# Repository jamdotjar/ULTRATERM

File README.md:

# ULTRATERM

ULTRATERM is a miniature replica of an ULTRAKILL settings terminal ( like the one used in cybergrind ), that acts as a bluetooth audio player.

> ***NOTE**: This project is built, but there's still work to do. Check out the [journal](JOURNAL.md) for progress updates! Right now I'm:* `bashing together some code`

## Design

The terminal sits at around 125mm tall, with a 57x104mm footprint. It was designed to look cool, be fairly accurate, and act as a (mostly) stand alone device. It features a:
- 2.8" TFT display
- Touchscreen + 3 physical buttons
- A 2000mAh battery
- Bluetooth headphone support
- USB-C storage interface
- Removable SD card storage ( and a custom microSD card adapter )
The case is designed to be entirely 3D printable, and assembled without adhesive or fasteners.
While the terminal isn't a perfect replica, it's decently close. ( for example, there's none of the wires near the top, but there is a magnetic attachment point so I *can* add them )

This project was made as mostly a fun intro to custom hardware. I've made keyboards before, but design wise those are fairly simplec ( this isn't much more complicated ). I decided to model it after the ULTRAKILL Cybergrind terminal because that's the one that handles  cybergrind music ingame ( and because its form factor is also a *lot* more forgiving to fit everything into )

If you happen to try and make your own, I'd suggest either 3d-printing it in blue for minimum effort, or printing it in grey, painting it, then scuffing the paint to give it the worn look it has in-game. ( also check out the assembly section )

I'm still hacking away at getting everything working, but here's a video demo of my progress so far:

## Gallery

*more in [./gallery](gallery)*

## PCB

## Case

### Wiring

## BOM 
*prices in usd, see [bom.csv](/BOM.CSV) too*
|Item                                        |Quantity|Price|Supplier  |Notes                                                             |link                                                                                                      |
|--------------------------------------------|--------|-----|----------|------------------------------------------------------------------|----------------------------------------------------------------------------------------------------------|
|PCB                                         |5       |4.7  |JLCPCB    |                                                                  |https://jlcpcb.com/                                                                                       |
|TINYPICO v2                                 |1       |20 | Digikey   |(+20 dollar shipping, ik its really expensive, I csn cover a good bit of the cost )|https://www.mouser.com/ProductDetail/392-TP-01                      |
|TZT 240x320 2.8" SPI ST7789V LCD Touch Panel|1       |7.09 |Aliexpress|                                                                  |https://www.aliexpress.com/item/1005004557916570.html                                                     |
|3.7v 2000mah LiPo battery                   |1       |16.92|Amazon    |price comparable to ali                                           |https://www.amazon.ca/Rechargeable-Controller-CUH-ZCT1-Electronic-Bluetooth/dp/B0CG178SHB                 |
|Pin Headers                                 |20      |2.00 |Aliexpress|for stupid LCD mounting soln.                                     |https://www.aliexpress.com/item/4000873858801                                                             |
|22Awg wire                                  |5m      |2.4  |Aliexpress|front panel mount + battery backup soln                           |https://www.aliexpress.com/item/1005004712828392.html                                                     |
|32gb microSD card                           |2       |4.7  |LCSC      |second waives 3$ fee, saves 1 dollar on order total               |https://lcsc.com/product-detail/Storage-products_SDTRUVAL-SDSDQAD-016G-SDWCK_C42416577.html               |
|32gb SD card                                |1       |5.8  |LCSC      |                                                                  |https://lcsc.com/product-detail/Storage-products_MK-MKSD032G-CGT1A_C22374946.html                         |
|LM809                                       |1       |0.66 |LCSC      |                                                                  |https://lcsc.com/product-detail/Supervisor-and-Reset-ICs_Texas-Instruments-LM809M3X-4-38-NOPB_C544520.html|
|JST-PH-2                                    |10      |0.59 |LCSC      |                                                                  |https://lcsc.com/product-detail/Wire-To-Board-Connector_JST-B2B-PH-K-K-LF-SN_C265438.html                 |
|SPDT slide switch                           |20      |0.48 |LCSC      |                                                                  |https://lcsc.com/product-detail/Slide-Switches_SHOU-HAN-SK12D07VG4_C393937.html                           |
|6mm pushbutton                              |50      |0.84 |LCSC      |                                                                  |https://lcsc.com/product-detail/Tactile-Switches_SHOU-HAN-TS665CJ_C393938.html                            |
|Amphenol 10067847-001RLF                    |1       |1.31 |LCSC      |                                                                  |https://lcsc.com/product-detail/SD-Card-Memory-Card-Connector_Amphenol-ICC-10067847-001RLF_C569097.html   |
|Hirose C719027                              |1       |1.04 |LCSC      |                                                                  |https://lcsc.com/product-detail/SD-Card-Memory-Card-Connector_HRS-Hirose-DM3D-SF_C719027.html             |
|LCSC Shipping                               |        |12.88|LCSC      |                                                                  |                                                                                                          |
|Total                                       |1       |95.21|          |                                                                  |                                                                                                          |
## Assembly

Putting this together is relatively simple, the hardest part is connecting the screen and front panel before putting the two halves together. Assuming you aren't too rough, the mounting holes for the screen and button panels should be enough to hold them. A small dab of superglue can help make sure they don't come out with repeated use. I'd advise dupont cables or soemthing similar to connect the screen, as long as it has a lot of slack it should be fine ( the case has a lot of empty space to wind the cables into )

## LICENSE

This project uses the [CC-BY-SA-4.0](https://creativecommons.org/licenses/by-sa/4.0/) for all firmware, documentation, renders, and other writing. Hardware including all Case and PCB designs, is licensed under the [CERN-OHL-W v2](https://ohwr.org/cern_ohl_w_v2.txt)
> This project was heavily inspired by the game ULTRAKILL, created by Hakita (Arsi "Hakita" Patala). The ULTRATERM design, as well as some assets used in renders are derived from or inspired by ULTRAKILL.
All rights to ULTRAKILL belong to Hakita and New Blood Interactive. This project is not affiliated with or endorsed by Hakita or New Blood. 
( [ULTRAKILL is a banger game, you should totally get it, it's like 20 bucks ](http://devilmayquake.com))

This project was made for [*highway*](https://highway.hackclub.com)

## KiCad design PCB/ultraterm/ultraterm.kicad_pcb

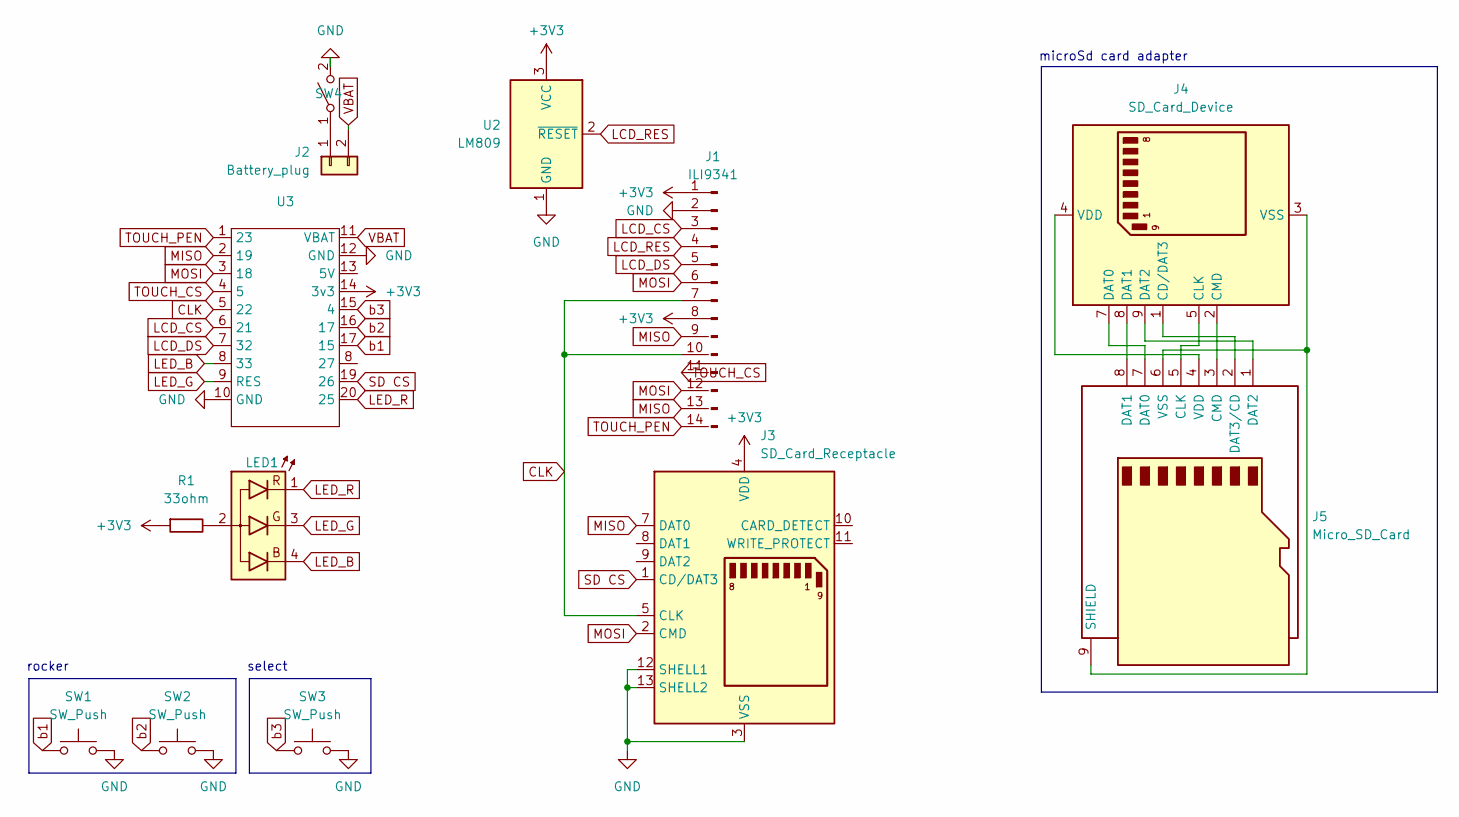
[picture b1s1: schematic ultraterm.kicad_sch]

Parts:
J1: ILI9341; PinHeader_1x11_P2.54mm_Vertical
J2: Battery_plug; JST_PH_B2B-PH-SM4-TB_1x02-1MP_P2.00mm_Vertical
J3: SD_Card_Receptacle; SD_Hirose_DM1AA_SF_PEJ82
J4: SD_Card_Device; SD_Card_Device_16mm_SlotDepth
J5: Micro_SD_Card; microSD_HC_Molex_104031-0811
LED1: LED_5mm_RGB_Kcom_RKGB; LED_D5.0mm-4_RGB_Wide_Pins
R1: 33ohm; R_Axial_DIN0207_L6.3mm_D2.5mm_P10.16mm_Horizontal
SW1, SW2, SW3: SW_Push; SW_PUSH_6mm
SW4: SW_SPST; SW_SPST_Omron_B3F-315x_Angled
U2: LM809; SOT-23
U3: TINYPICO

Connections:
+3V3: J1.1 (VCC), J1.8 (LED), J3.4 (VDD), R1.1, U2.3 (VCC), U3.14 (3v3)
CLK: J1.7 (SCK), J1.10 (CLK), J3.5 (CLK), U3.5 (22)
GND: J1.2 (GND), J3.3 (VSS), J3.6 (VSS), J3.12 (SHELL1), J3.13 (SHELL2), SW1.2, SW2.2, SW3.2, SW4.2 (B), U2.1 (GND), U3.10 (GND), U3.12 (GND)
LCD_CS: J1.3 (CS), U3.6 (21)
LCD_DS: J1.5 (DC/RS), U3.7 (32)
LCD_RES: J1.4 (RESET), U2.2 (~RESET)
LED_B: LED1.4 (B), U3.8 (33)
LED_G: LED1.3 (G), U3.9 (RES)
LED_R: LED1.1 (R), U3.20 (25)
MISO: J1.9 (MISO), J1.13 (T_DO), J3.7 (DAT0), U3.2 (19)
MOSI: J1.6 (MOSI), J1.12 (T_DIN), J3.2 (CMD), U3.3 (18)
unnamed: J2.1, SW4.1 (A)
unnamed: J4.1 (CD/DAT3), J5.2 (DAT3/CD)
unnamed: J4.5 (CLK), J5.5 (CLK)
unnamed: J4.2 (CMD), J5.3 (CMD)
unnamed: J4.7 (DAT0), J5.7 (DAT0)
unnamed: J4.8 (DAT1), J5.8 (DAT1)
unnamed: J4.9 (DAT2), J5.1 (DAT2)
unnamed: J4.4 (VDD), J5.4 (VDD)
unnamed: J4.3 (VSS), J4.6 (VSS), J5.6 (VSS), J5.9 (SHIELD)
unnamed: LED1.2 (A), R1.2
SD CS: J3.1 (CD/DAT3), U3.19 (26)
TOUCH_CS: J1.11 (T_CS), U3.4 (5)
TOUCH_PEN: J1.14 (T_IRQ), U3.1 (23)
VBAT: J2.2, U3.11 (VBAT)
b1: SW1.1, U3.17 (15)
b2: SW2.1, U3.16 (17)
b3: SW3.1, U3.15 (4)

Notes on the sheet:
microSd card adapter
rocker
select

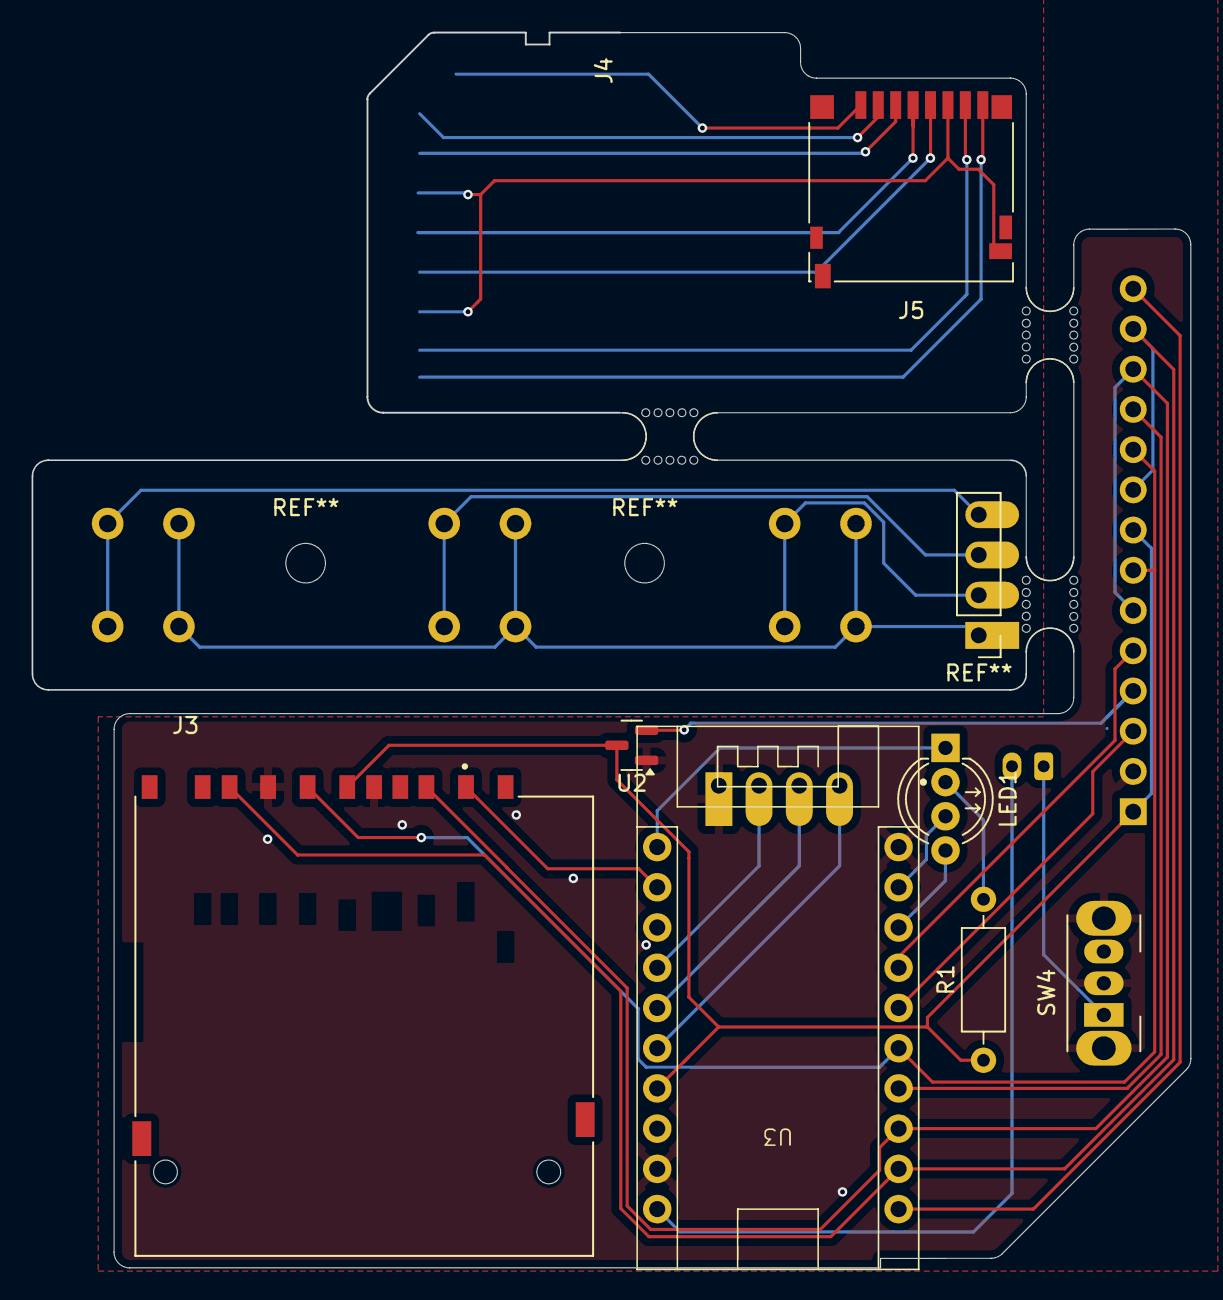
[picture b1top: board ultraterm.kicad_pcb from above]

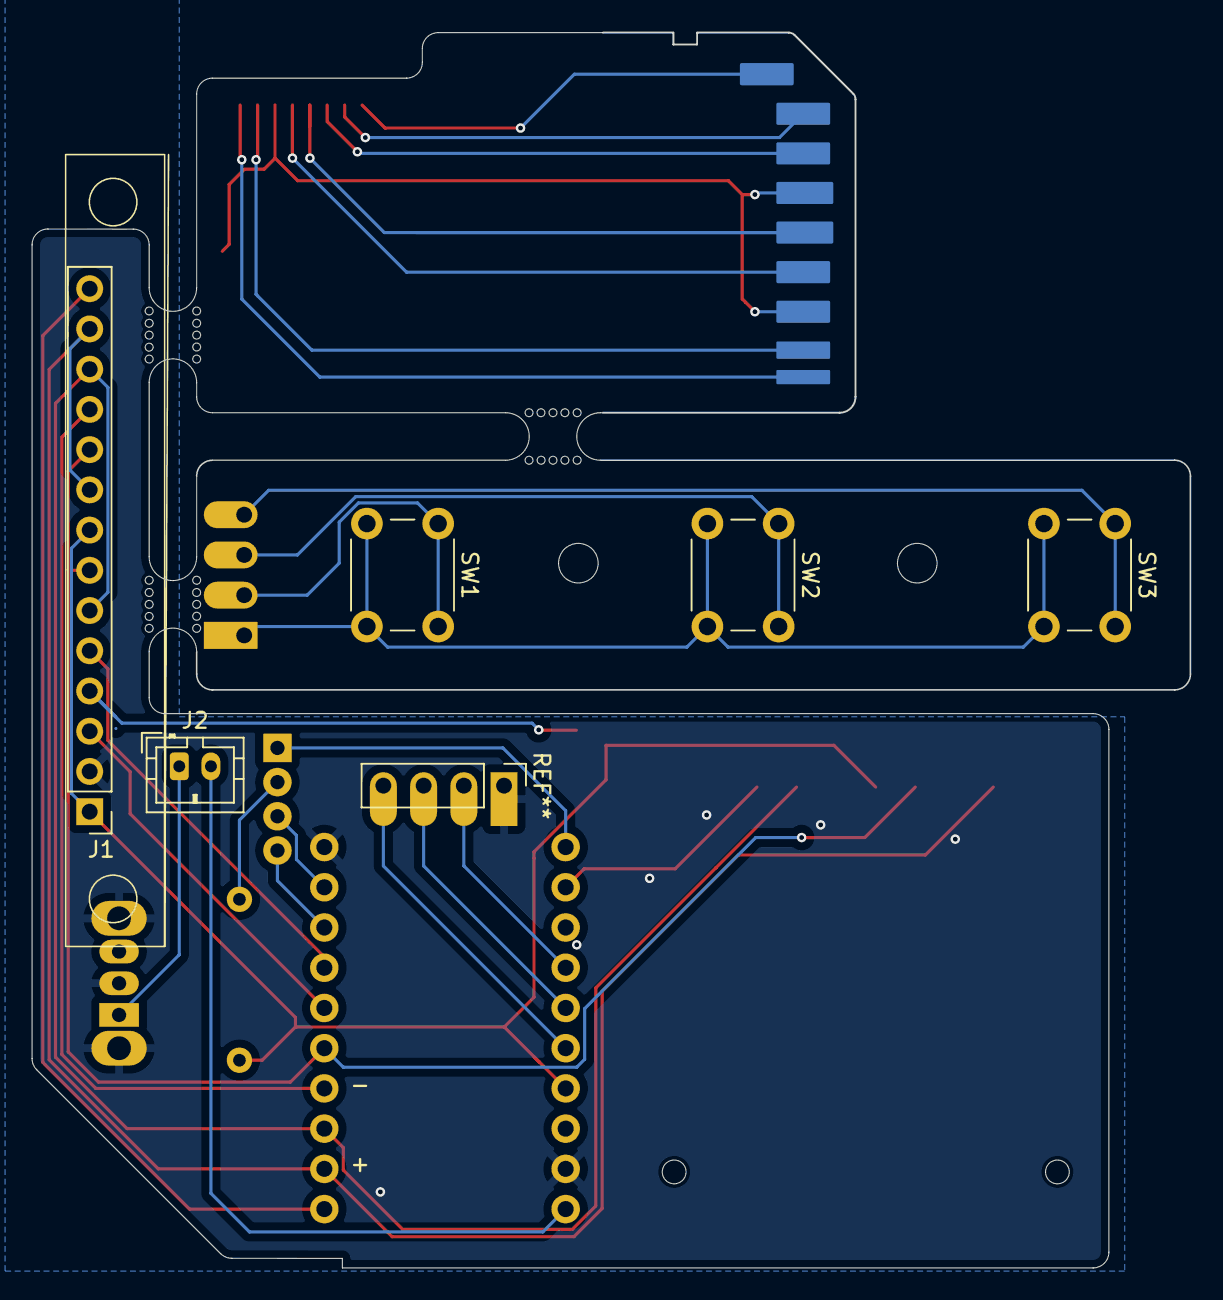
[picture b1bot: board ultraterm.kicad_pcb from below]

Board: 2 copper layers, 73.1 x 78.0 mm, 16 parts (5 on the bottom side), 28 nets.

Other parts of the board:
mouse-bite-3mm-slot, mouse-bite-3mm-slot#2, mouse-bite-3mm-slot#3: VAL**; mouse-bite-3mm-slot

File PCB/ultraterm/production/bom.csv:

Designator,Footprint,Quantity,Value,LCSC Part #
J1,PinHeader_1x14_P2.54mm_Vertical,1,ILI9341,
J2,JST_PH_B2B-PH-K_1x02_P2.00mm_Vertical,1,Battery_plug,
J3,AMPHENOL_10067847-001RLF,1,SD_Card_Receptacle,
J4,SD_Card_Device_16mm_SlotDepth,1,SD_Card_Device,
J5,microSD_HC_Hirose_DM3D-SF,1,Micro_SD_Card,
"MOUSE-BITE-3MM-SLOT_3, MOUSE-BITE-3MM-SLOT_2, MOUSE-BITE-3MM-SLOT",mouse-bite-3mm-slot,3,VAL**,
"SW1, SW2, SW3",SW_PUSH_6mm,3,SW_Push,
SW4,SW_Slide_SPDT_Angled_CK_OS102011MA1Q,1,SW_SPST,
U1,XIAO-ESP32S3-SMD,1,XIAO-ESP32-S3-SMD,
U2,SOT-23,1,LM809,

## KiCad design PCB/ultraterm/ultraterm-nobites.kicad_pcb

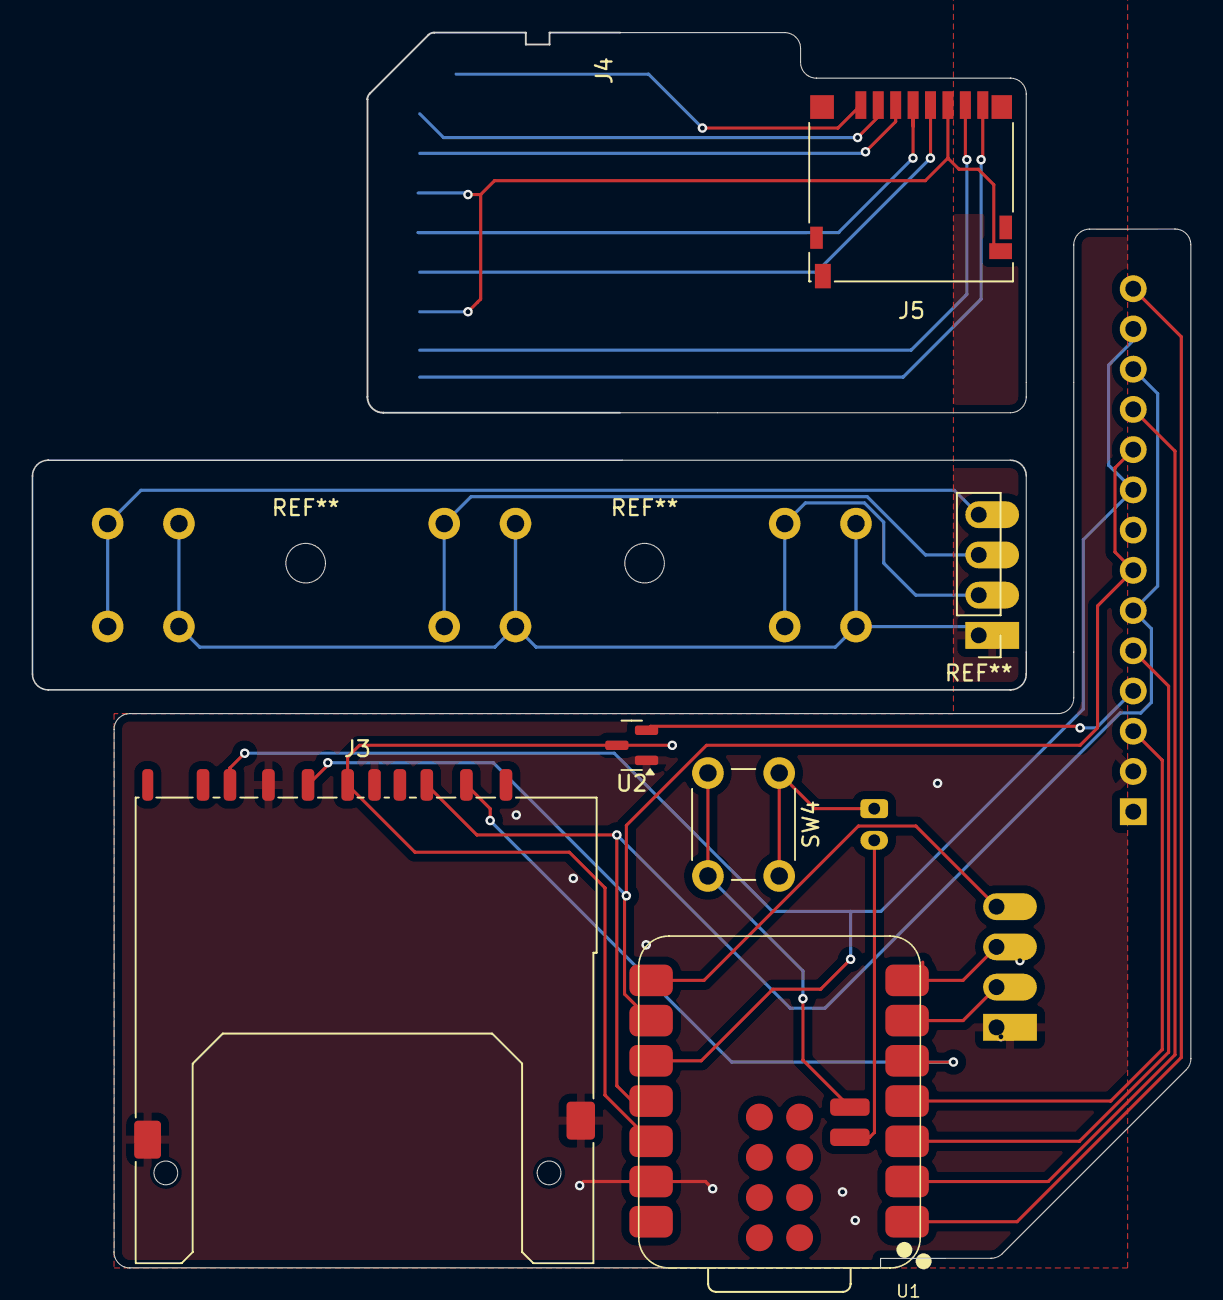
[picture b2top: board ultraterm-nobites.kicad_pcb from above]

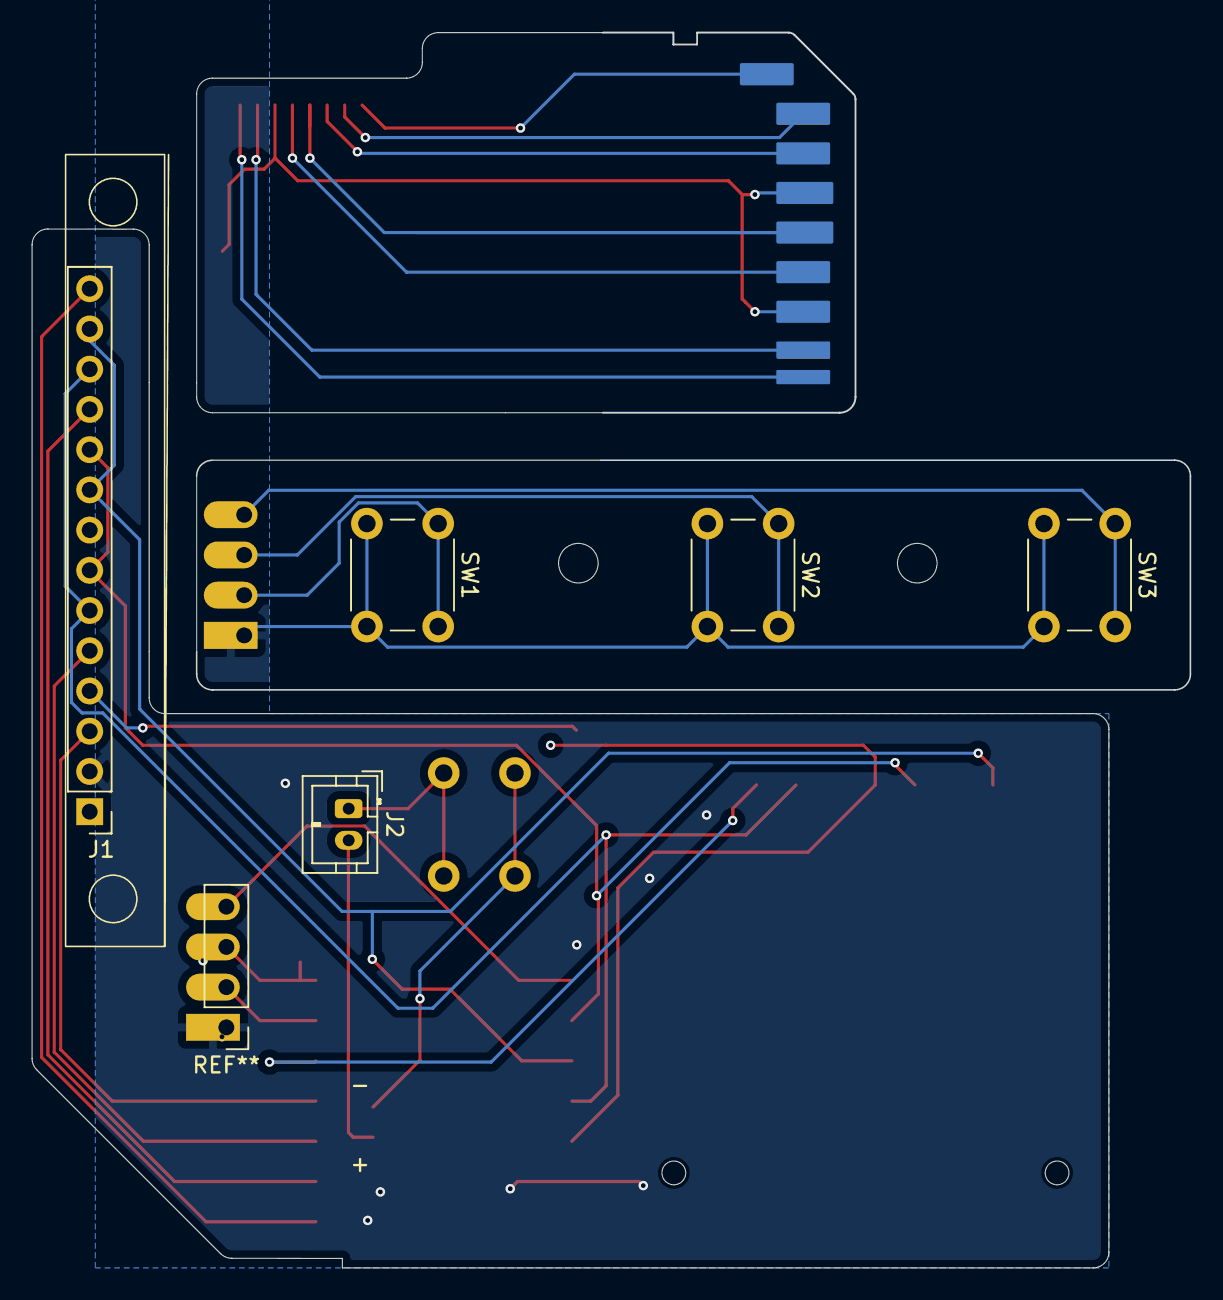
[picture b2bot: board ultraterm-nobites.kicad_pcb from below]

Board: 2 copper layers, 73.1 x 78.0 mm, 11 parts (5 on the bottom side), 25 nets.

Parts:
J1: ILI9341; PinHeader_1x14_P2.54mm_Vertical
J2: Battery_plug; JST_PH_B2B-PH-K_1x02_P2.00mm_Vertical
J3: SD_Card_Receptacle; SD_Kyocera_145638009511859+
J4: SD_Card_Device; SD_Card_Device_16mm_SlotDepth
J5: Micro_SD_Card; microSD_HC_Hirose_DM3D-SF
SW1, SW2, SW3: SW_Push; SW_PUSH_6mm
SW4: SW_SPST; SW_PUSH_6mm_H13mm
U1: XIAO-ESP32-S3-SMD; XIAO-ESP32S3-SMD
U2: LM809; SOT-23

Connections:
+3V3: J1.1 (VCC), J1.8 (LED), J3.4 (VDD), U1.12 (3V3), U2.3 (VCC)
GND: J1.2 (GND), J3.3 (VSS), J3.6 (VSS), J3.12 (SHELL1), J3.13 (SHELL2), SW1.2, SW2.2, SW3.2, U1.13 (GND), U2.1 (GND)
LCD_CS: J1.3 (CS), U1.4 (GPIO4_A3_D3)
LCD_DS: J1.5 (DC/RS), U1.3 (GPIO3_A2_D2)
LCD_RES: J1.4 (RESET), U2.2 (~RESET)
MISO: J1.9 (MISO), J1.13 (T_DO), J3.7 (DAT0), U1.10 (GPIO8_A9_D9_MISO)
MOSI: J1.6 (MOSI), J1.12 (T_DIN), J3.2 (CMD), U1.11 (GPIO9_A10_D10_MOSI)
unnamed: J1.7 (SCK), J1.10 (CLK), J3.5 (CLK), U1.9 (GPIO7_A8_D8_SCK)
unnamed: J2.1, SW4.1 (A)
unnamed: J2.2, U1.16 (GND)
unnamed: J4.1 (CD/DAT3), J5.2 (DAT3/CD)
unnamed: J4.5 (CLK), J5.5 (CLK)
unnamed: J4.2 (CMD), J5.3 (CMD)
unnamed: J4.7 (DAT0), J5.7 (DAT0)
unnamed: J4.8 (DAT1), J5.8 (DAT1)
unnamed: J4.9 (DAT2), J5.1 (DAT2)
unnamed: J4.4 (VDD), J5.4 (VDD)
unnamed: J4.3 (VSS), J4.6 (VSS), J5.6 (VSS), J5.9 (SHIELD)
unnamed: SW4.2 (B), U1.15 (BAT)
SD CS: J3.1 (CD/DAT3), U1.5 (GPIO5_A4_D4_SDA)
TOUCH_CS: J1.11 (T_CS), U1.2 (GPIO2_A1_D1)
TOUCH_PEN: J1.14 (T_IRQ), U1.1 (GPIO1_A0_D0)
b1: SW1.1, U1.6 (GPIO6_A5_D5_SCL)
b2: SW2.1, U1.7 (GPIO43_A6_D6_TX)
b3: SW3.1, U1.8 (GPIO44_D7_RX)

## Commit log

2025-05-19 init commit
2025-05-20 Planning stages still
2025-06-28 added literally all the pcb files because i forgot
2025-07-03 Revised for TINYPICO
2025-07-03 fiddled with PCB for export
2025-07-03 Created firmware template
2025-07-03 Semifinal case design
2025-07-04 audio connection, no playback
2025-07-04 gitignore changes
2025-07-04 jul3
2025-07-05 IO seems good?
2025-07-05 input handler loop
2025-07-06 Final beta firmware.
2025-07-06 Final case ver.
2025-07-06 Final renders, repo cleanup
2025-07-06 more renders
2025-07-07 added gallery renders, and license information
2025-07-07 Final README changes before submission.
2025-07-07 small fix
2025-07-07 fix to the fix
2025-07-07 BOM.CSV
2025-07-07 fix image not displaying
2025-07-07 this might fix the csv
2025-07-07 done all the renders
2025-08-07 commit before i start scrwing with stuff again
2025-08-13 it actually works for sure this time ( still no screen )
2025-08-13 working music play (w/o screen)
2025-08-13 added assembly photos
2025-08-13 playlist, skipping, pause all functional
2025-08-15 readme
2025-08-15 Rename README to README.html
2025-08-15 Rename README.html to README.md
